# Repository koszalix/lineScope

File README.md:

# Index
1. [Overview](#Overview)
2. [Key features](#key_features)
3. [Specification](#specification)
4. [Modules](#construction)
  - [Voltage probe](#voltage_probe)
  - [0.5A probe](#05A_probe)
  - [5A probe](#5A_probe)
  - [Relay board](#relay_board)
  - [Isolators](#isolators)
5. [Mechanical constructions](#Mechanical_construction)  
6. [Bringup](#Bringup)
# Overview 

lineScope is an oscilloscope attachment for  safe measurement of AC lines. Two current ranges (0.5A/5A) and one voltage range (260V) are supported. 

The lineScope construction is fully modular, so range can be change easily just by change of sense module. 

# Key Features 
- Separate socket for `DUT` power and devices power 
- `260V` Voltage measurement range 
- `0.5A` and `5A` current measurement range 
- Overvoltage and overcurrent protection
- Switchable output 
- `BNC` connectors for easy oscilloscope connection 

# Specification

## Voltage measurement
- Measurement range `260V`
- `DUT` voltage to output voltage ratio 1mV/V
- Output noise level `<2mV`
- Frequency response 10Hz - 10kHz<!-- Need to be checked against real device-->
- Dielectric strength `2kV 1min`
- Linearity `<1%`
- Uncertainty `<5%`

## Current measurement
- Measurement range `5A` or `0.5A`
- `DUT` current to output voltage `1 mA/mV` for `0.5A` range; `10 mA/mV` for `5A` range
- Output noise level `<2mV`
- Frequency response 10Hz - 10kHz<!-- Need to be checked against real device-->
- Dielectric strength `2kV 1min`
- Linearity `<1%`
- Uncertainty `<5%`

## Operating conditions 
- Temperature `15-35`
- Humidity `20-70 RH`

# Modules
Construction of the `lineScope` is fully modular, for basic operation only `Voltage probe`, `Isolators`  and `0.5A probe` or `5A probe` is  required. 
However it's recommended to have full setup with `Relay board` and two current probes.  Connections between modules are presented at diagram bellow.

## Voltage probe
### General description
The voltage probe transform 230V AC line voltage into mV range with galvanic separation. Voltage transformation is done by TV19G current transformer, connected in series with known resistance (150k) into AC line.
### Input protection
Input of AC line  is protected by 600Vrms GDT and 275Vrms MOX, however is highly recommended to use  proper surge protection power cord. 

### Input voltage range
The board is designed for 230V AC line input however any voltage from 1V to 260Vrms should work. 

The probe should be connected parallel to AC line. 

### Output voltage range
Output voltage is proportional to input voltage, the ratio is equal to 1:1000 (1mV/V). Maximum output voltage should not exceed 300mV range.

### Single ended or differential output

By default board output is single ended, however pcb can be switched to differential output, to switch pcb to differential output the `R4` resistor must be removed and `RV2, DZ3, DZ4` should be mounted. 

### Connectors 
Board is equipped with pass trough connectors for both line and neutral. Standard 2.54mm pin headers are used for the output connector, pinout table is presented bellow.

| Designator | Pin | Description                               |
| ---------- | --- | ----------------------------------------- |
| J1         | 1   | AC Line - Phase                           |
| J3         | 1   | AC Line - Phase                           |
| J2         | 1   | AC Line - Neutral                         |
| J4         | 1   | AC Line - Neutral                         |
| J5         | 1   | SE output \| Differential output positive |
| J5         | 2   | GND                                       |
| J5         | 3   | GND \| Differential output negative       |
## 0.5A probe
### Overview 
The 0.5A probe is current probe, designed to transform current into voltage, the nominal measured current is 0.5A and output voltage is 1.5V maximum. 

### Input current range and protection
The rated probe current is 0.5A, current larger than 0.5A can permanently destroy the the PCB, or cause dielectric breakdown. 

The probe should be connected in series with load.

AC Input is protected only by 5x20mm 500mA ceramic fuse, keep in mind that 5x20 fuses can only work up to 250V, if you plan to work with higher voltages you should consider board modification. 

### Output voltage 
The output voltage is proportional to input current, with 1:3 ratio (3mV/mA). Maximum output voltage should not exceed 1.5Vrms for nominal probe current(0.5A) 

### Single ended or differential output

By default board output is single ended, however pcb can be switched to differential output, to switch pcb to differential output the `R2` resistor must be removed and `RV2, DZ3, DZ4` should be mounted. 

# Connectors 

Board is equipped with 3 AC line connectors, and one standard 90 degree 2,54mm pin headers for output. 

Connectors pinout is presented at table bellow. 

| Designator | Pin | Description                                |
| ---------- | --- | ------------------------------------------ |
| J1         | 1   | AC Line input                              |
| J3         | 1   | AC Line pass trough                        |
| J2         | 1   | AC Line output                             |
| J4         | 1   | SE output \| Differential output possitive |
| J4         | 2   | GND                                        |
| J4         | 3   | GND \| Differential output negative        |
## 5A probe
### Overview
The 5A probe is current probe, designed to transform current into voltage, the nominal measured current is 5A and output voltage is 1.5V maximum. 

### Input current range and protection
The rated probe current is 5A, current larger than 5A can permanently destroy the the PCB, or cause dielectric breakdown. 

The probe should be connected in series with load.

AC Input is protected only by 5x20mm 5A ceramic fuse, keep in mind that 5x20 fuses can only work up to 250V, if you plan to work with higher voltages you should consider board modification. 

###  Output voltage 
The output voltage is proportional to input current, with 1:300 ratio (300mV/A). Maximum output voltage should not exceed 1.5Vrms for nominal probe current(5A).

### Single ended or differential output

By default board output is single ended, however pcb can be switched to differential output, to switch pcb to differential output the `R4` resistor must be removed and `RV2, DZ3, DZ4` should be mounted. 

### Connectors 

Board is equipped with 3 AC line connectors, and one standard 90 degree 2,54mm pin headers for output. 

Connectors pinout is presented at table bellow. 

| Designator | Pin | Description                                |
| ---------- | --- | ------------------------------------------ |
| J1         | 1   | AC Line input                              |
| J3         | 1   | AC Line pass trough                        |
| J2         | 1   | AC Line output                             |
| J4         | 1   | SE output \| Differential output possitive |
| J4         | 2   | GND                                        |
| J4         | 3   | GND \| Differential output negative        |
## Relay board
### Overview 
The relay board is designed for selecting current probes and switching the output, for output switching both line and neutral is switched off. 

### Switching capability 
All relays, tracks and connectors are rated for `16A/250V` AC line switching. 

### Relay board
All relays are mounted in standard 7.5mm relays sockets, to change faulty relay no soldering is required.  

Relays coils are rated for 12V DC, back emf diodes are present on the PCB. 

The `Relpol RM85-1011-35-2012` are used, but any `16A` rated, `12V` coil relay can be used for replacemnt
### Connectors 

For HV standard 6.3mm tab connectors are used, for low voltage/control JST-XH connectors are used. 

Connectors pinout at presented in table bellow

| Designator | Pin | Description            |
| ---------- | --- | ---------------------- |
| J1         | 1   | Neutral in             |
| J3         | 1   | Neutral out            |
| J2         | 1   | Line out               |
| J4         | 1   | Line high current in   |
| J6         | 1   | Line low current in    |
| J5         | 1   | VCC                    |
| J5         | 2   | Line `ON/OFF`          |
| J5         | 3   | Range selection        |
| J5         | 4   | Neutral `ON/OFF`       |
| J5         | 5   | GND                    |
| J7         | 1   | AC Power (low voltage) |
| J7         | 2   | AC Power (low voltage) |
## Isolator board

### Overview 
The `Isolator board` is designed as carrier board for  the probes modules and as second layer of galvanic isolation. 

### Connecting the probes
Voltage probe must be connected to the `J3` connector, current probes must be connected to `J4` and `J5` connectors. 

### Connectors 

| Designator | Pin | Description               |     |
| ---------- | --- | ------------------------- | --- |
| J1         | 1   | AC power grid side        |     |
| J1         | 2   | AC power grid side        |     |
| J2         | 1   | AC power scope side       |     |
| J2         | 2   | AC power scope side       |     |
| J3         | 1   | Voltage probe signal      |     |
| J3         | 2   | Voltage probe GND         |     |
| J3         | 3   | Voltage probe GND         |     |
| J4         | 1   | Current probe signal      |     |
| J4         | 2   | Current probe GND         |     |
| J4         | 3   | Current probe GND         |     |
| J5         | 1   | Current probe signal      |     |
| J5         | 2   | Current probe GND         |     |
| J5         | 3   | Current probe GND         |     |
| J7         | 1   | Voltage output hot        |     |
| J7         | 2   | Voltage output cold       |     |
| J8         | 1   | Current output hot        |     |
| J8         | 2   | Current output cold       |     |
| J9         | 1   | VCC2                      |     |
| J9         | 2   | Select probe low current  |     |
| J9         | 3   | Select probe high current |     |
| J9         | 4   | GND                       |     |

# Mechanical Construction 

# Bringup

Bringup was descried [[Bringup | here]]

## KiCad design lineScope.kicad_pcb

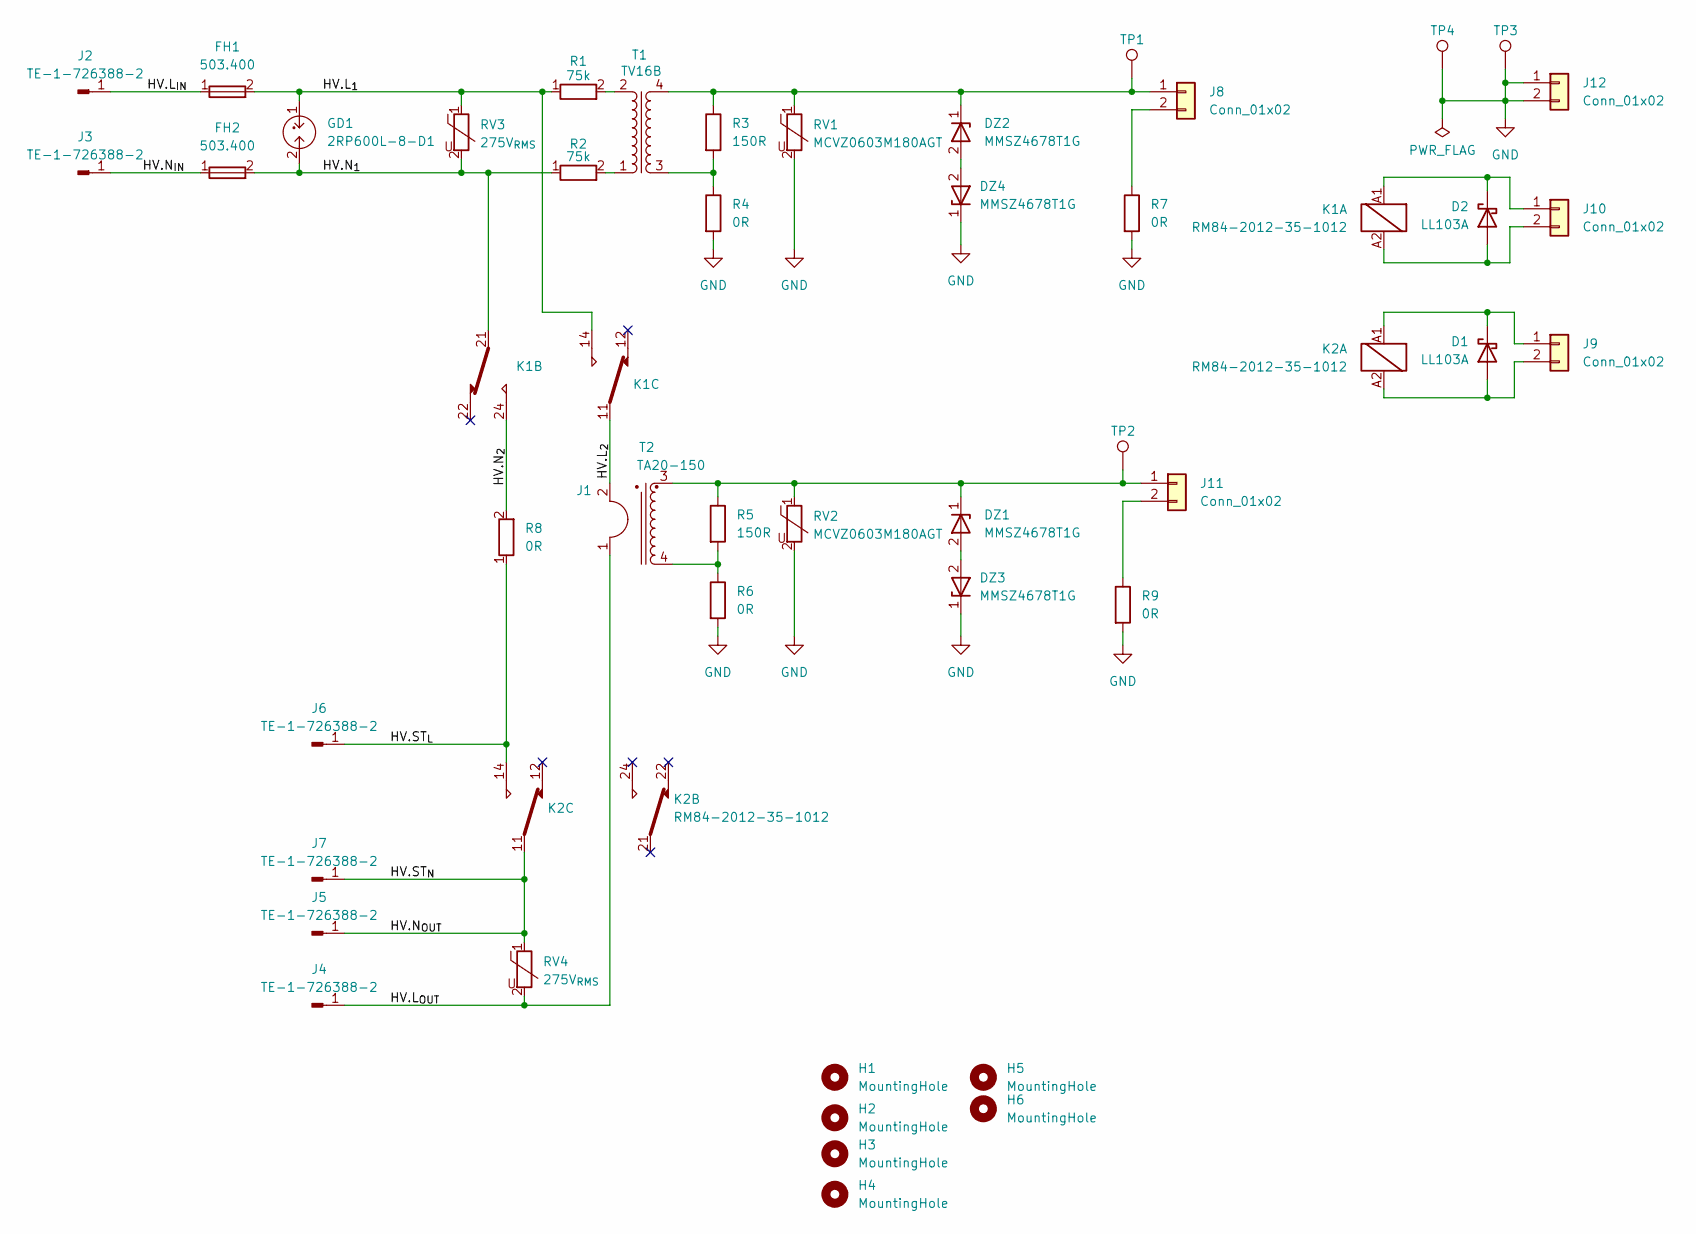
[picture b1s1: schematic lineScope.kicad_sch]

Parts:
D1, D2: LL103A; D_MiniMELF; MPN LL103A
DZ1, DZ2, DZ3, DZ4: 1V8; D_SOD-123; MPN MMSZ4678T1G
FH1, FH2: 503.400; ESKA_503.400; MPN 503.400
GD1: 2RP600L-8-D1; YAGEO_2RP; MPN 2RP600L-8-D1
H1, H2, H3, H4, H5, H6: MountingHole; MountingHole_3.2mm_M3
J1: BodgeWire_P25_H16.5_B4_SQ1.5_1
J2, J3, J4, J5, J6, J7: TE-1-726388-2; MPN TE-1-726388-2
J8, J9, J10, J11, J12: Conn_01x02; JST_XH_B2B-XH-A_1x02_P2.50mm_Vertical
K1, K2: RM84-2012-35-1012; RM84; MPN RM84-2012-35-1012
R1, R2: 75k; R_Axial_DIN0309_L9.0mm_D3.2mm_P15.24mm_Horizontal; MPN MF50 75K
R3, R5: 150R; R_0603_1608Metric; Tolerance 1%; MPN RC0603FR-07150R
R4, R6: 0R; R_0603_1608Metric; Tolerance 1%; MPN RC0603FR-07150R
R7, R9: 0R; R_0603_1608Metric; Tolerance 1%; MPN RC0603FR-070R
R8: 0R; R_Axial_DIN0411_L9.9mm_D3.6mm_P20.32mm_Horizontal; MPN MBB02070Z0000ZC100
RV1, RV2: MCVZ0603M180AGT; R_0603_1608Metric_Pad0.98x0.95mm_HandSolder; MPN MCVZ0603M180AGT
RV3, RV4: 275V_{RMS}; RV_Disc_D9mm_W5.2mm_P5mm; MPN MOV-07D471KK
T1: TV16; PowerUC-TV16; MPN TV16B
T2: TA20-150; PowerUC-TA20; MPN TA20-150
TP1, TP2, TP3, TP4: TestPoint; TestPoint_Loop_D2.54mm_Drill1.5mm_Beaded

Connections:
/HV.L_{1}: FH1.2, GD1.1, K1.14, R1.1, RV3.1
/HV.L_{2}: J1.2, K1.11
/HV.L_{IN}: FH1.1, J2.1
/HV.L_{OUT}: J1.1, J4.1, RV4.2
/HV.N_{1}: FH2.2, GD1.2, K1.21, R2.1, RV3.2
/HV.N_{2}: K1.24, R8.2
/HV.N_{IN}: FH2.1, J3.1
/HV.N_{OUT}: J5.1, J7.1, K2.11, RV4.1
/HV.ST_{L}: J6.1, K2.14, R8.1
GND: DZ3.1, DZ4.1, J12.1, J12.2, R4.2, R6.2, R7.2, R9.2, RV1.2, RV2.2, TP3.1, TP4.1
unnamed: D1.2 (A), J9.2, K2.A2
unnamed: D1.1 (K), J9.1, K2.A1
unnamed: D2.2 (A), J10.2, K1.A2
unnamed: D2.1 (K), J10.1, K1.A1
unnamed: DZ1.2, DZ3.2
unnamed: DZ2.2, DZ4.2
unnamed: DZ2.1, J8.1, R3.1, RV1.1, T1.4, TP1.1
unnamed: J8.2, R7.1
unnamed: DZ1.1, J11.1, R5.1, RV2.1, T2.3, TP2.1
unnamed: J11.2, R9.1
unnamed: R1.2, T1.2
unnamed: R2.2, T1.1
unnamed: R3.2, R4.1, T1.3
unnamed: R5.2, R6.1, T2.4

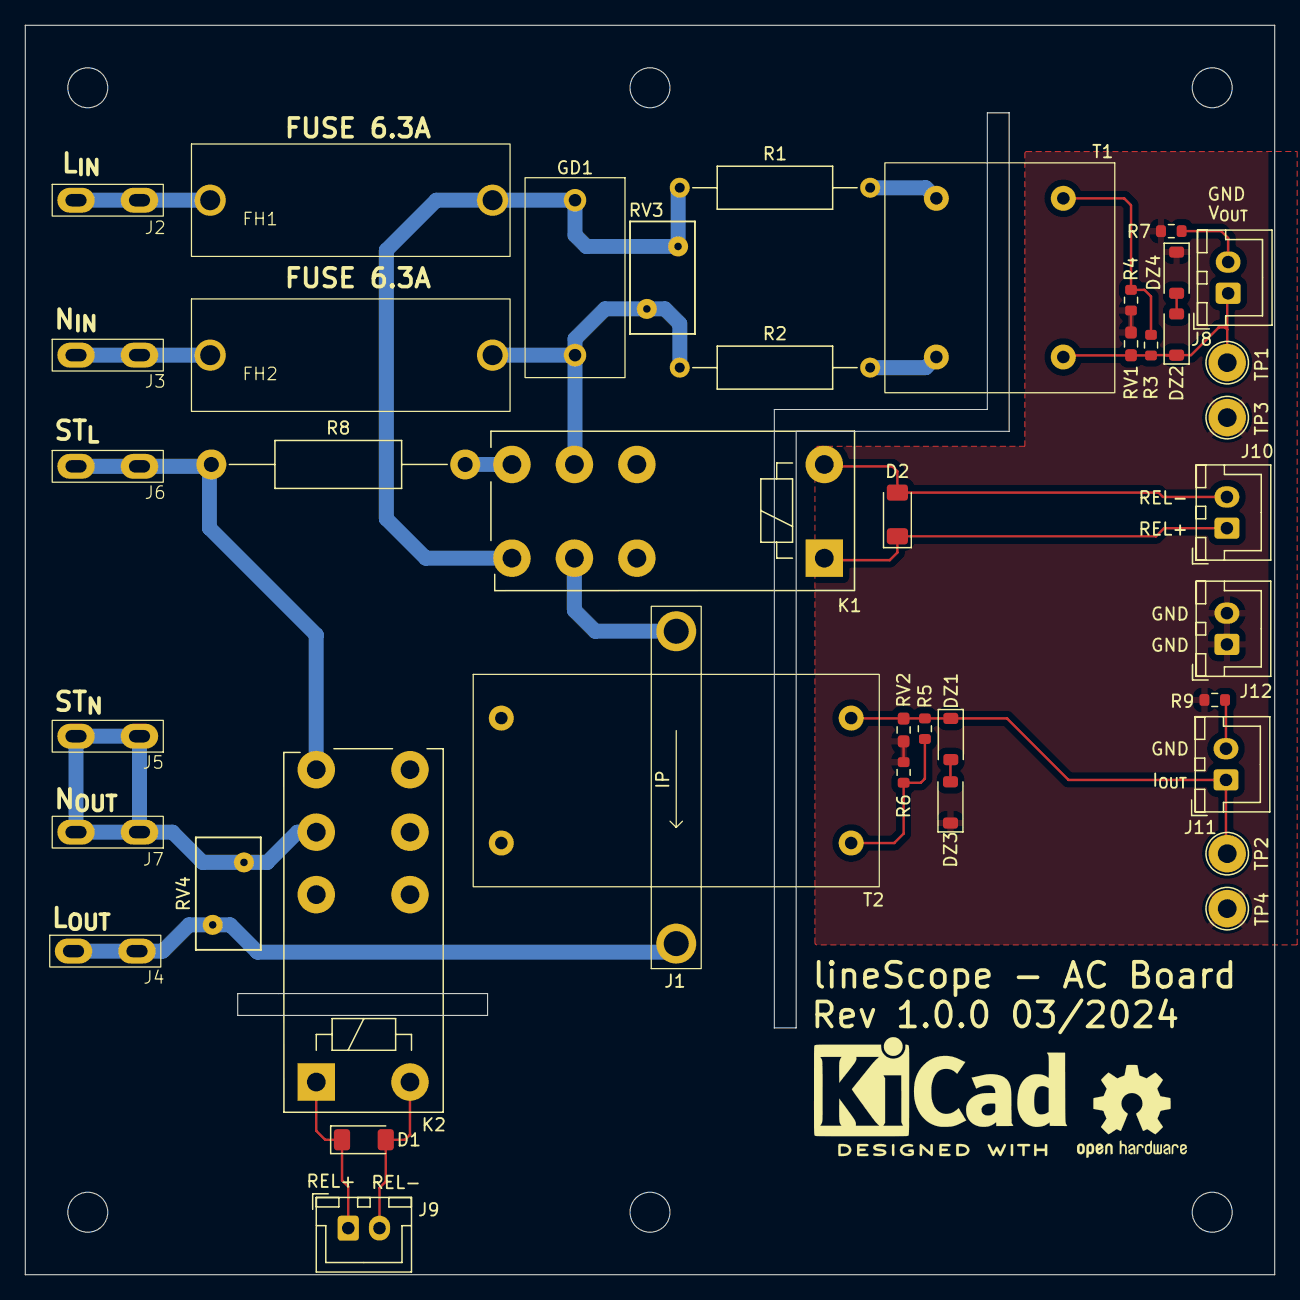
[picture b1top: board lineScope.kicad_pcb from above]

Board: 2 copper layers, 100.0 x 100.0 mm, 48 parts (0 on the bottom side), 24 nets.

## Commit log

2024-03-17 Create schematic
2024-03-17 Route board
2024-04-11 Remove PCB files
2024-04-11 Add Readme
2024-05-26 Update current output parameters
2024-06-01 Add block diagram drawio
2024-06-01 Add measurement
2024-11-07 Add images
